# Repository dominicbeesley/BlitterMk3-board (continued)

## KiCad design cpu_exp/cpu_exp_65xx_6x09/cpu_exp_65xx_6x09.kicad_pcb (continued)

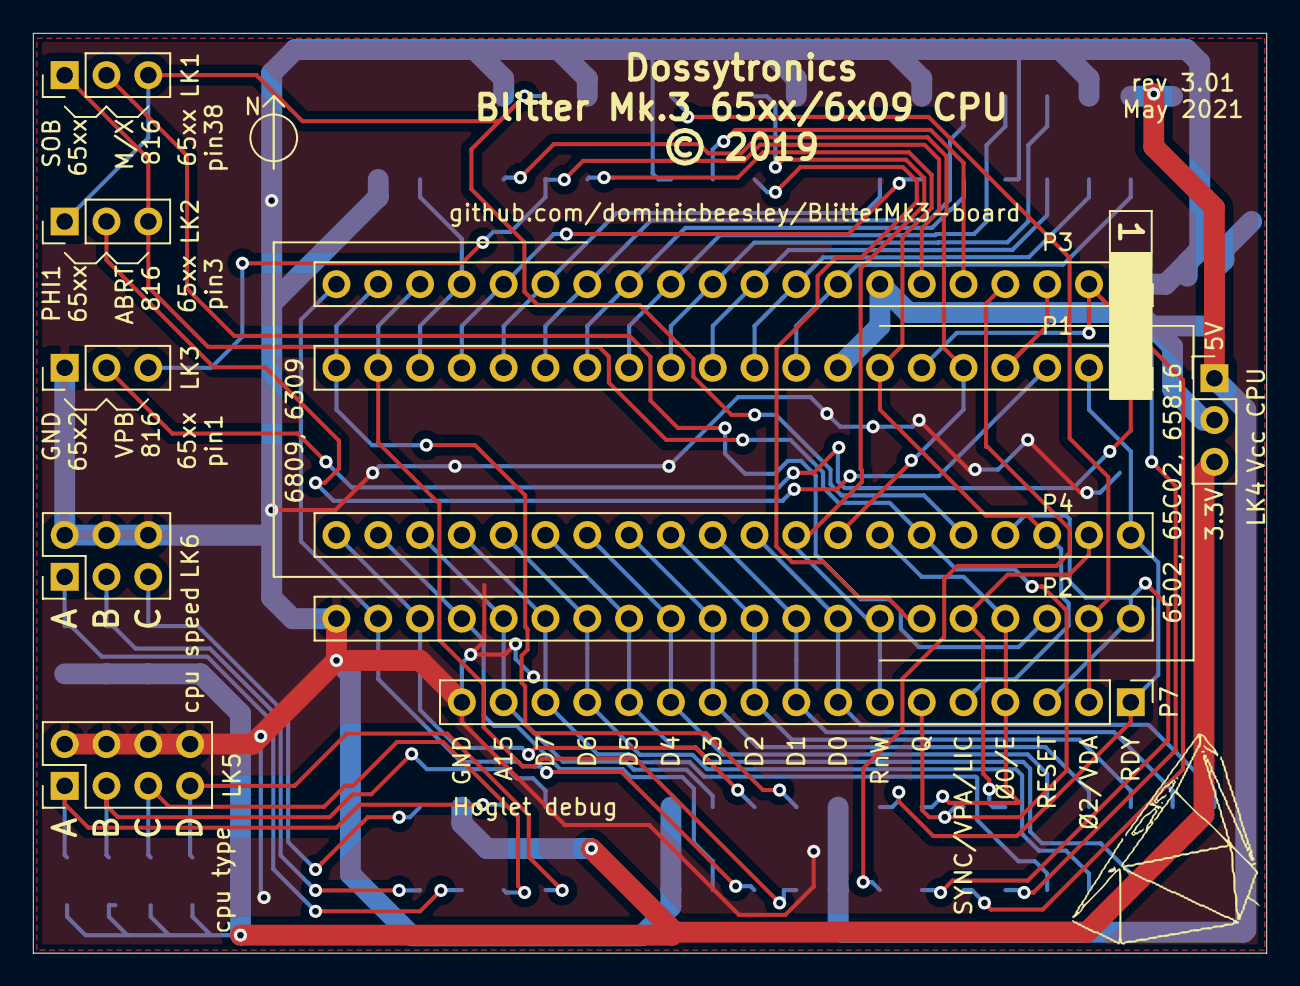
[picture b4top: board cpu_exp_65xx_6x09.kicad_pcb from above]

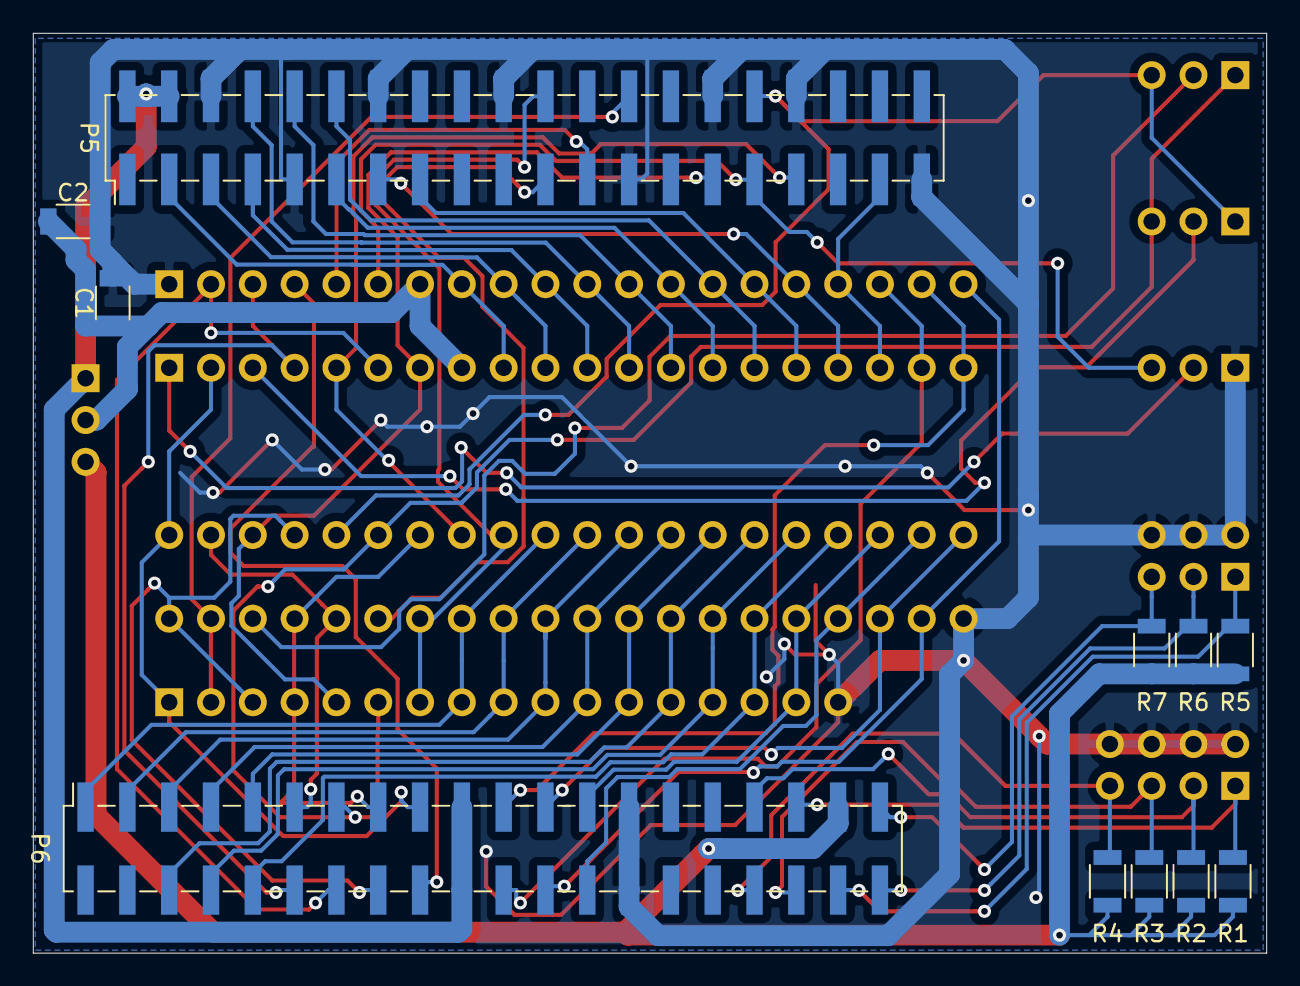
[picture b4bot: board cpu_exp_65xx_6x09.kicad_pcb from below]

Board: 2 copper layers, 74.9 x 55.9 mm, 22 parts (11 on the bottom side), 54 nets.

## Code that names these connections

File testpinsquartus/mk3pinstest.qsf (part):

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set_location_assignment PIN_P13 -to "HDMI_D0_o(n)"
set_location_assignment PIN_T14 -to HDMI_HPD_i
set_location_assignment PIN_T15 -to HDMI_SCL_o
set_location_assignment PIN_R14 -to HDMI_SDA_io
set_location_assignment PIN_R15 -to SYS_PHI2_o
set_location_assignment PIN_N14 -to SYS_SYNC_o
set_location_assignment PIN_N16 -to SYS_PHI1_o
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set_location_assignment PIN_E16 -to SYS_BUF_D_DIR_o


set_location_assignment PIN_B16 -to exp_PORTG_nOE
set_location_assignment PIN_B15 -to SYS_nNMI_i
set_location_assignment PIN_C16 -to SYS_nIRQ_i
set_location_assignment PIN_C15 -to SYS_RDY_i
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set_location_assignment PIN_A5 -to exp_PORTEFG_io[2]
set_location_assignment PIN_B4 -to exp_PORTEFG_io[1]
set_location_assignment PIN_A4 -to exp_PORTEFG_io[0]
set_location_assignment PIN_B3 -to exp_PORTF_nOE
set_location_assignment PIN_A3 -to exp_PORTE_nOE

set_location_assignment PIN_F11 -to exp_PORTB_o[7]
set_location_assignment PIN_A14 -to exp_PORTB_o[6]
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

set_location_assignment PIN_T8  -to I2C_SCL_o
set_location_assignment PIN_R9  -to I2C_SDA_io
set_location_assignment PIN_R8	-to SUP_nRESET_i

set_location_assignment PIN_F5  -to MEM_RAM_nCE_o[0]
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
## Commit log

2021-07-16 Export from SVN #301
2021-08-17 Mk.3 fixes and new 68000 expansion board
2021-09-10 Updates from SVN to rev3.03
2021-12-09 Add fixit notes to 68000 cpu board for next revision
2021-12-09 Add pin mappings for 6800 card
2021-12-09 NEW: 6800 cpu card
